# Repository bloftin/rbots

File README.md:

# rbots
RTEAM Robotics Club repository

Our club website: http://rteamrobotics.weebly.com/

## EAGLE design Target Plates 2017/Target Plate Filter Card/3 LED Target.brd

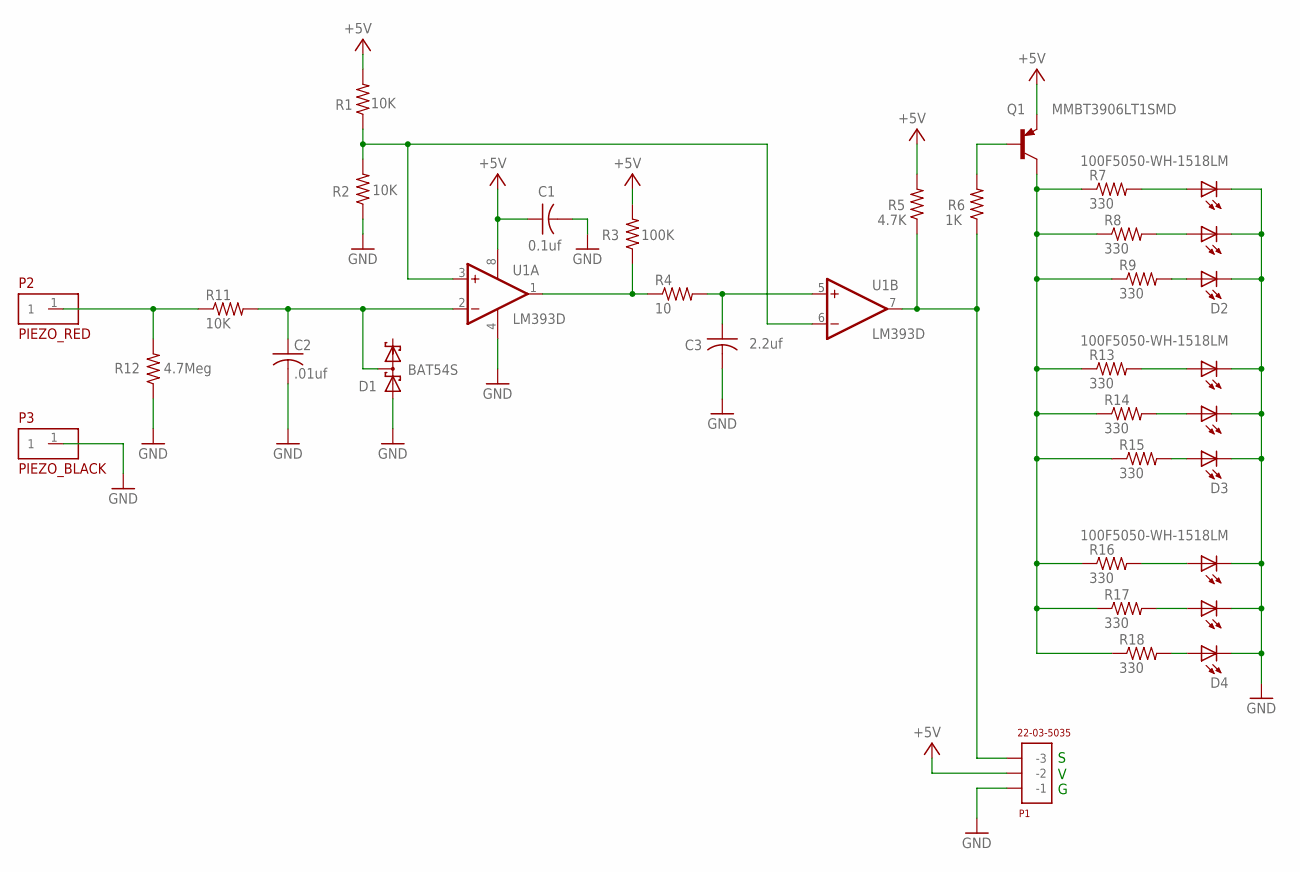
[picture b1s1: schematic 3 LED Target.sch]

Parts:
C1: 0.1uf; C0603
C2: .01uf; C0603
C3: 2.2uf; C1206
D1: BAT54S; SOT23
D2, D3, D4: 100F5050-WH-1518LM; LED5050
P1: 22-03-5035; MOLEX3_STRAIGHT
P2: PIEZO_RED; PADHOLE
P3: PIEZO_BLACK; PADHOLE
Q1: MMBT3906LT1SMD; SOT23-BEC
R1, R2, R11: 10K; R0603
R3: 100K; R0603
R4: 10; R0603
R5: 4.7K; R0603
R6: 1K; R0603
R7, R8, R9, R13, R14, R15, R16, R17, R18: 330; R0603
R12: 4.7Meg; R0603
U1: LM393D; SO08

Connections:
+5V: C1.1, P1.2 (-2), Q1.E, R1.2, R3.2, R5.2, U1.8 (V+)
GND: C1.2, C2.2, C3.2, D1.1 (A1), D2.4 (C2), D2.5 (C1), D2.6 (C), D3.4 (C2), D3.5 (C1), D3.6 (C), D4.4 (C2), D4.5 (C1), D4.6 (C), P1.1 (-1), P3.1, R2.1, R12.1, U1.4 (V-)
unnamed: P2.1, R11.1, R12.2
unnamed: C2.1, D1.3 (C1A2), R11.2, U1.2 (-IN)
unnamed: R1.1, R2.2, U1.3 (+IN), U1.6 (-IN)
unnamed: Q1.B, R6.2
unnamed: R3.1, R4.1, U1.1 (OUT)
unnamed: C3.1, R4.2, U1.5 (+IN)
unnamed: Q1.C, R7.1, R8.1, R9.1, R13.1, R14.1, R15.1, R16.1, R17.1, R18.1
unnamed: D2.1 (A), R7.2
unnamed: D2.2 (A1), R8.2
unnamed: D2.3 (A2), R9.2
unnamed: D3.1 (A), R13.2
unnamed: D3.2 (A1), R14.2
unnamed: D3.3 (A2), R15.2
unnamed: D4.1 (A), R16.2
unnamed: D4.2 (A1), R17.2
unnamed: D4.3 (A2), R18.2
unnamed: P1.3 (-3), R5.1, R6.1, U1.7 (OUT)

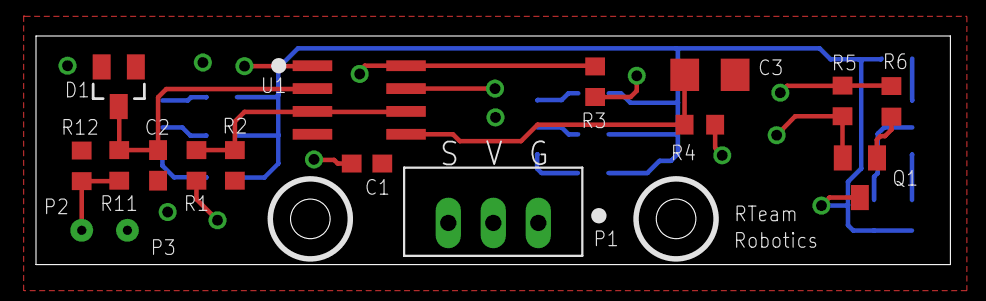
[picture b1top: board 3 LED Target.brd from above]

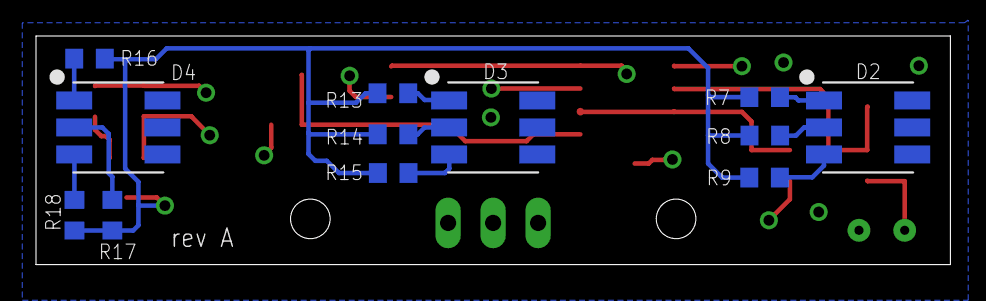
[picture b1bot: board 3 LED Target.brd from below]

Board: 4 copper layers, 50.8 x 12.7 mm, 29 parts (12 on the bottom side), 19 nets.

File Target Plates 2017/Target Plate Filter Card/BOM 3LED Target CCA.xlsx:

| Bill of Materials for 3LED Target Circuit Card Assembly
Reference Designator | Description | Manufacturer | Part Number | Distributor | Distributor Part Number | Quantity | Piece Price | Total Price
R1, R2, R11 | 10K, 0603, resistor | Vishay Dale | CRCW060310K0FKEA | Digikey | 541-10.0KHCT-ND | 3 | 0.1 | 0.30000000000000004
R3 | 100K, 0603, resistor | Vishay Dale | CRCW0603100KFKEA | Digikey | 541-100KHCT-ND | 1 | 0.1 | 0.1
R4 | 10 ohm, 0603, resistor | Vishay Dale | CRCW060310R0FKEA | Digikey | 541-10.0HCT-ND | 1 | 0.1 | 0.1
R5 | 4.7K, 0603, resistor | Vishay Dale | CRCW06034K70FKEA | Digikey | 541-4.70KHCT-ND | 1 | 0.1 | 0.1
R6 | 1K, 0603, resistor | Vishay Dale | CRCW06031K00FKEA | Digikey | 541-1.00KHCT-ND | 1 | 0.1 | 0.1
R7, R8, R9, R13, R14, R15, R16, R17, R18 | 330 ohm, 0603, resistor | Vishay Dale | CRCW0603330RFKEA | Digikey | 541-330HCT-ND | 1 | 0.1 | 0.1
R12 | 4.7 Megohm, 0603, resistor | Vishay Dale | CRCW06034M70FKEA | Digikey | 541-4.70MHCT-ND |  | 0.1 | 0.1
C1 | 0.1 uF, X7R, 0603, capacitor | Vishay Vitramon | VJ0603Y104KXXCW1BC | Digikey | 720-1379-1-ND | 1 | 0.1 | 0.1
C2 | .01 uF, X7R, 0603, capacitor | Vishay Vitramon | VJ0603Y103KXACW1BC | Digikey | 720-1531-1-ND | 1 | 0.1 | 0.1
C3 | 2.2 uF, X7R, 1206, capacitor | TDK Corp. | C3216X7R1E225K160AA | Digikey | 445-1382-1-ND | 1 | 0.24 | 0.24
D1 | Schottky dual diode, SOT23 | Vishay Semiconductor | BAT54S-E3-08 | Digikey | BAT54S-E3-08CT-ND | 1 | 0.32 | 0.32
D2, D3, D4 | Triple LED, 6000K, 15-18LM, white, (100 quantity for $7.13) | Chanzon | 100F5050-WH-1518LM | Amazon | 100F5050-WH-1518LM | 3 | 7.1300000000000002E-2 | 0.21390000000000001
Q1 | PNP transistor, SOT23 | On Semiconductor | MMBT3906LT1G | Digikey | MMBT3906LT1GOSCT-ND | 1 | 0.1 | 0.1
U1 | Dual comparator | ST Microelectronics | LM393DT | Digikey | 497-1593-1-ND | 1 | 0.39 | 0.39
P1 | 3 pin connector, keyed, 2.5 mm pitch, vertical | Molex | 22-03-5035 | Digikey | WM18887-ND | 1 | 0.5 | 0.5
 |  |  |  |  |  |  | Total | 2.8639000000000001
Misc other parts not on Circuit card assembly
 | Description | Manufacturer | Part Number | Distributor | Distributor Part Number | Quantity | Piece Price
 | Piezo Buzzer, 24mm, plastic housing, wire leads | CUI Inc. | CEP-1110 | Digikey | 102-1144-ND | 1 | 1.78
 | Latex Tubing, #804, 3/8in OD, 1/4in ID, 1/16in wall thickness, black, 1 ft long | Kent Elastomer | #804, 1 foot | Amazon | Serach: latex tubing (#804) 1 FT BLACK | 1 | 3.99
 | Black velcro, 7 in x 0.4 in |  |  |  |  | 1
 | 2mm bolts |  |  | McMaster-Carr |  | 4
 | 2mm nuts |  |  | McMaster-Carr |  | 6

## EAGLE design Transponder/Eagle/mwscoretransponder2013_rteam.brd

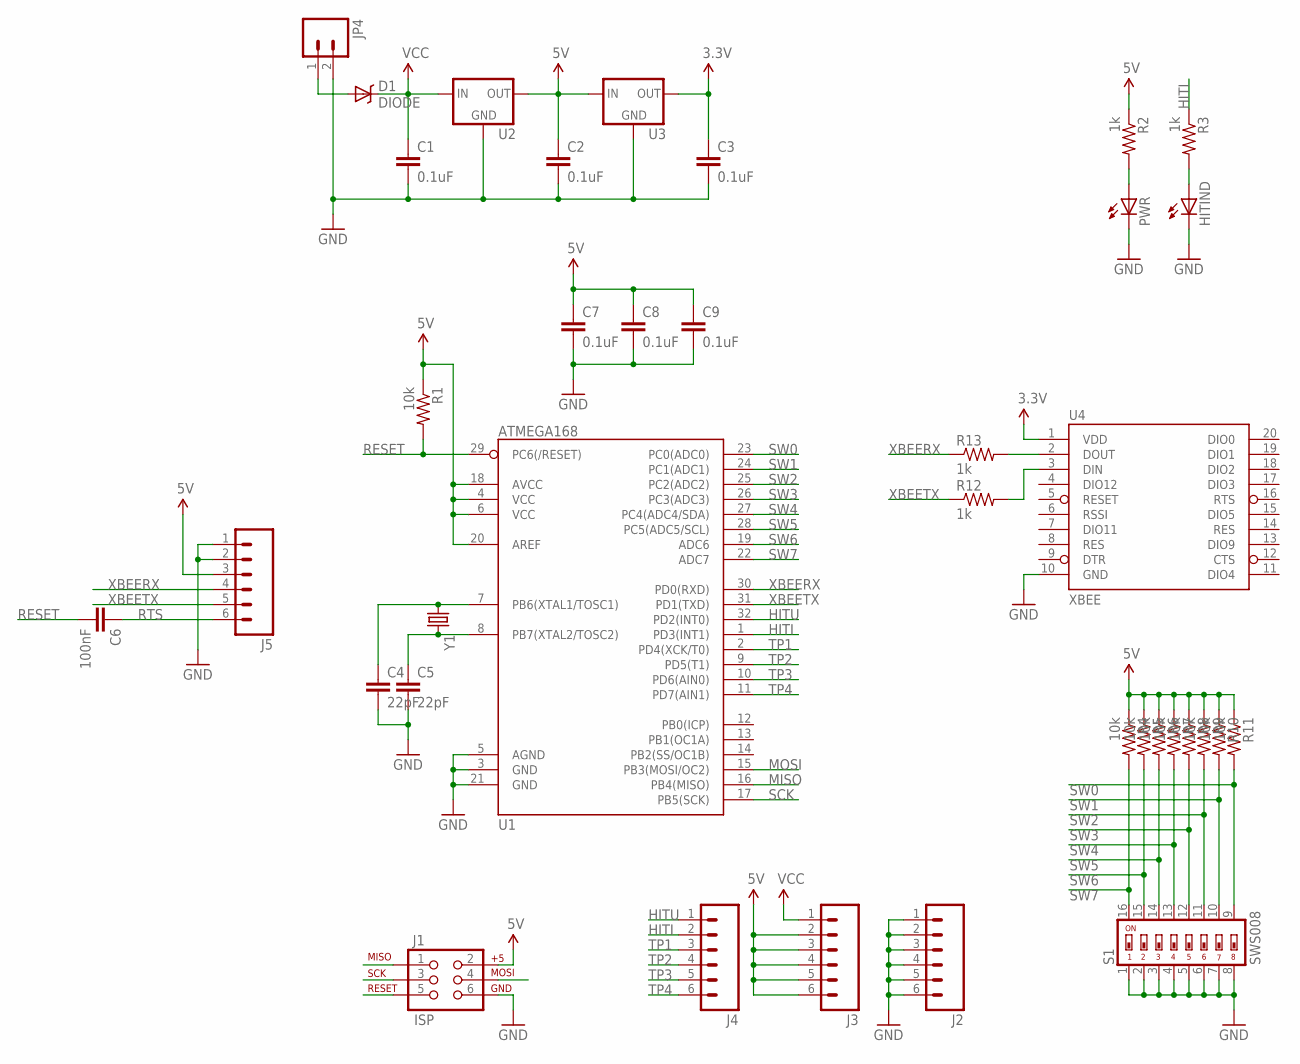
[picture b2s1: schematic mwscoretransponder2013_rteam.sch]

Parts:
C1, C2, C3, C7, C8, C9: 0.1uF; 0603-CAP
C4, C5: 22pF; 0603-CAP
C6: 100nF; 0603-CAP
D1: DIODE; SMA-DIODE
HITIND: LED0603; LED-0603
J1: ISP; 2X3
J2, J3, J4, J5: M06SIP; 1X06
JP4: M023.5MM_LOCK; SCREWTERMINAL-3.5MM-2_LOCK
PWR: LED0603; LED-0603
R1, R4, R5, R6, R7, R8, R9, R10, R11: 10k; 0603-RES
R2, R3, R12, R13: 1k; 0603-RES
S1: SWS008; SMS-008
U1: ATMEGA168; TQFP32-08
U2, U3: V_REG_MIC2920; SOT223
U4: XBEE; XBEE-SMD
Y1: CRYSTAL5X3; CRYSTAL-SMD-5X3

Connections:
3.3V: C3.1, U3.3 (OUT), U4.1 (VDD)
5V: C2.1, C7.1, C8.1, C9.1, J1.2, J3.2, J3.3, J3.4, J3.5, J3.6, J5.3, R1.1, R2.1, R4.1, R5.1, R6.1, R7.1, R8.1, R9.1, R10.1, R11.1, U1.4 (VCC), U1.6 (VCC), U1.18 (AVCC), U1.20 (AREF), U2.3 (OUT), U3.1 (IN)
GND: C1.2, C2.2, C3.2, C4.2, C5.2, C7.2, C8.2, C9.2, HITIND.C, J1.6, J2.1, J2.2, J2.3, J2.4, J2.5, J2.6, J5.1, J5.2, JP4.2, PWR.C, S1.1, S1.2, S1.3, S1.4, S1.5, S1.6, S1.7, S1.8, U1.3 (GND), U1.5 (AGND), U1.21 (GND), U2.2 (GND), U3.2 (GND), U4.10 (GND)
HITI: J4.2, R3.1, U1.1 (PD3(INT1))
HITU: J4.1, U1.32 (PD2(INT0))
MISO: J1.1, U1.16 (PB4(MISO))
MOSI: J1.4, U1.15 (PB3(MOSI/OC2))
unnamed: PWR.A, R2.2
unnamed: HITIND.A, R3.2
unnamed: C4.1, U1.7 (PB6(XTAL1/TOSC1)), Y1.1
unnamed: D1.A, JP4.1
unnamed: C5.1, U1.8 (PB7(XTAL2/TOSC2)), Y1.3 (2)
unnamed: R13.2, U4.2 (DOUT)
unnamed: R12.2, U4.3 (DIN)
RESET: C6.2, J1.5, R1.2, U1.29 (PC6(/RESET))
RTS: C6.1, J5.6
SCK: J1.3, U1.17 (PB5(SCK))
SW0: R11.2, S1.9, U1.23 (PC0(ADC0))
SW1: R10.2, S1.10, U1.24 (PC1(ADC1))
SW2: R9.2, S1.11, U1.25 (PC2(ADC2))
SW3: R8.2, S1.12, U1.26 (PC3(ADC3))
SW4: R7.2, S1.13, U1.27 (PC4(ADC4/SDA))
SW5: R6.2, S1.14, U1.28 (PC5(ADC5/SCL))
SW6: R5.2, S1.15, U1.19 (ADC6)
SW7: R4.2, S1.16, U1.22 (ADC7)
TP1: J4.3, U1.2 (PD4(XCK/T0))
TP2: J4.4, U1.9 (PD5(T1))
TP3: J4.5, U1.10 (PD6(AIN0))
TP4: J4.6, U1.11 (PD7(AIN1))
VCC: C1.1, D1.C, J3.1, U2.1 (IN)
XBEERX: J5.4, R13.1, U1.30 (PD0(RXD))
XBEETX: J5.5, R12.1, U1.31 (PD1(TXD))

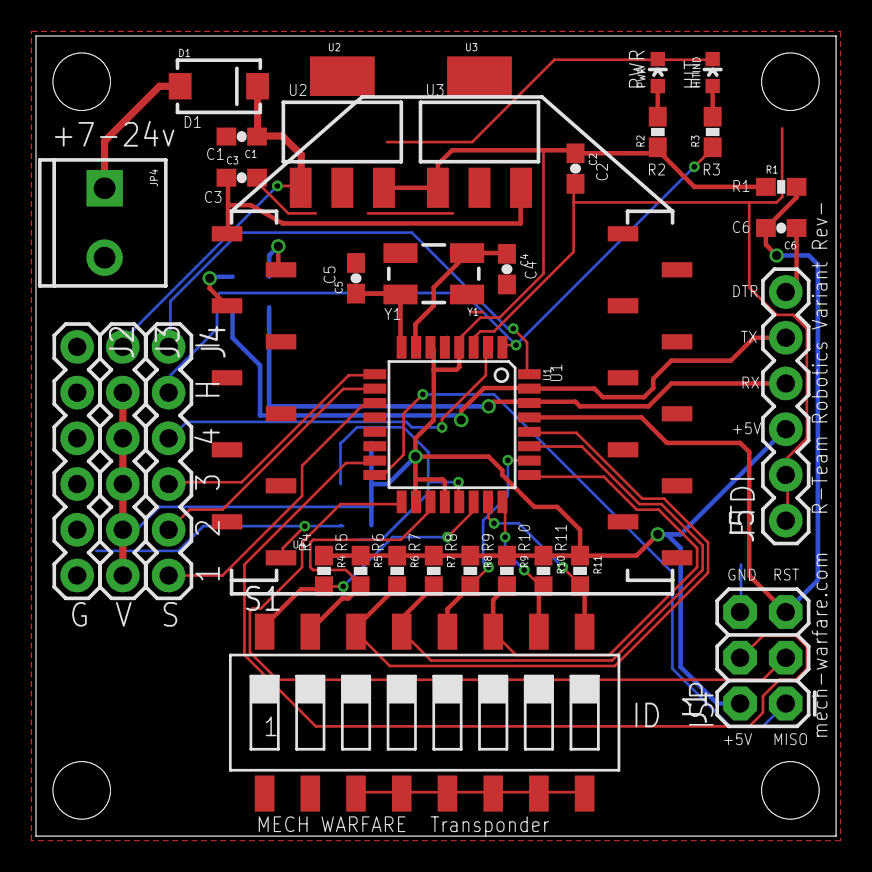
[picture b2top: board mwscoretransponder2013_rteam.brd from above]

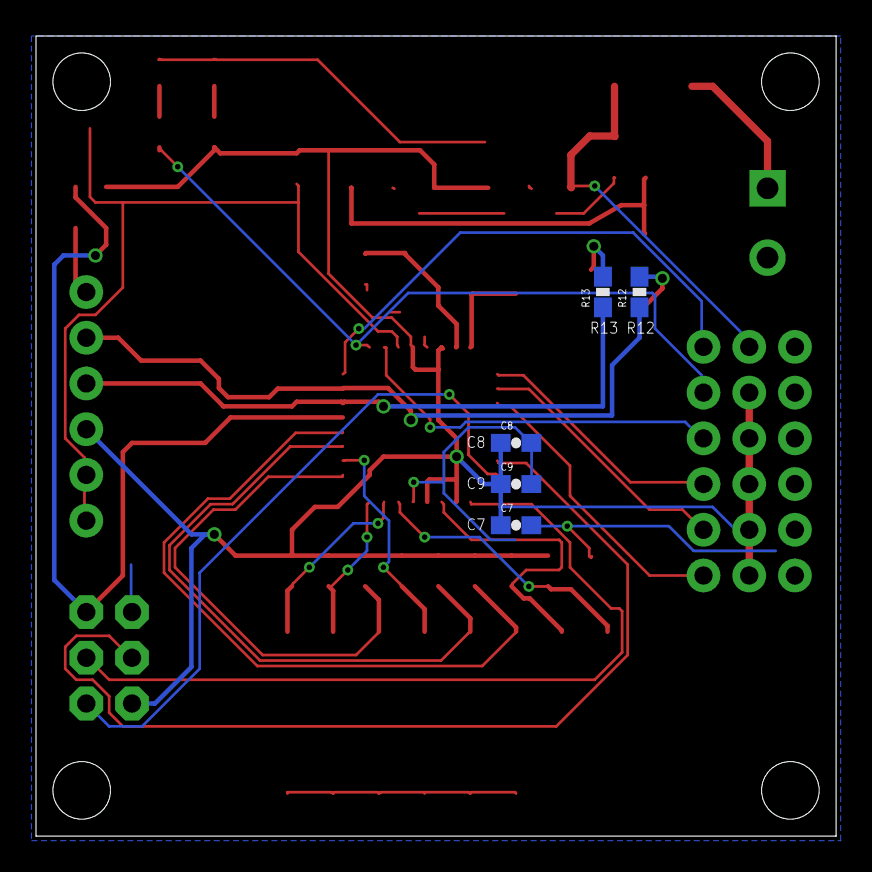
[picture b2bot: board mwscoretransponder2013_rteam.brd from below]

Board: 2 copper layers, 44.5 x 44.5 mm, 37 parts (5 on the bottom side), 32 nets.

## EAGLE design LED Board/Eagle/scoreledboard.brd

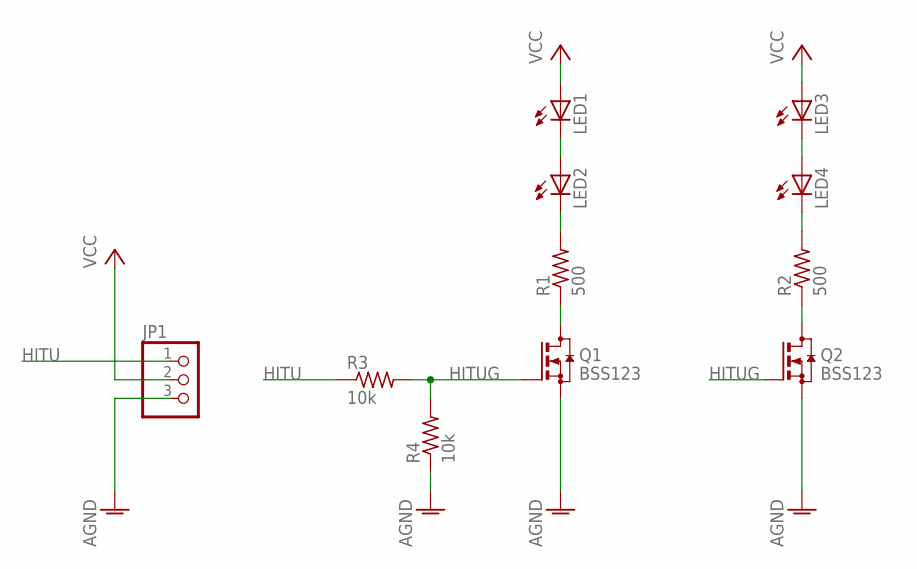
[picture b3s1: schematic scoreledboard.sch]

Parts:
JP1: PINHD-1X3; 1X03
LED1, LED2, LED3, LED4: LEDCHIPLED_1206; CHIPLED_1206
Q1, Q2: BSS123; SOT23
R1, R2: 500; R1206
R3, R4: 10k; R1206

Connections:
AGND: JP1.3, Q1.2 (S), Q2.2 (S), R4.1
HITU: JP1.1, R3.1
HITUG: Q1.1 (G), Q2.1 (G), R3.2, R4.2
unnamed: LED1.C, LED2.A
unnamed: LED2.C, R1.2
unnamed: Q1.3 (D), R1.1
unnamed: LED3.C, LED4.A
unnamed: LED4.C, R2.2
unnamed: Q2.3 (D), R2.1
VCC: JP1.2, LED1.A, LED3.A

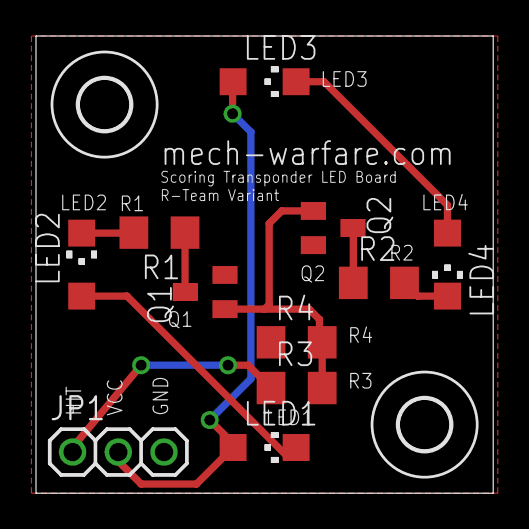
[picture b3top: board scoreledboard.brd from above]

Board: 2 copper layers, 25.4 x 25.4 mm, 13 parts (0 on the bottom side), 10 nets.

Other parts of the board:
U$1, U$2: 2,8

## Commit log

2015-04-29 Initial LED and transponder design
    Initial LED and transponder design for Mech Warfare target plates
2015-04-29 Archive test
    Archive test
2015-04-29 archive
    archive
2015-04-30 initial target plate design
    initial target plate design
2015-04-30 Archive lego mindstorms
    Archive lego mindstorms
2015-04-30 Archive Arduino
    Archive Arduino
2015-04-30 Archive Arduino 2
    Archive Arduino 2
2015-04-30 Archive Droid
    Archive Droid
2015-04-30 Archive Droid 2
    Archive Droid 2
2015-04-30 Archive Droid 3
    Archive Droid 3
2015-04-30 Archive Droid 4
    Archive Droid 4
2015-04-30 Archive Droid 5
    Archive Droid 5
2015-04-30 Archive Droid 6
    Archive Droid 6
2015-04-30 Archive Droid 7
    Archive Droid 7
2015-04-30 Archive Droid 8
    Archive Droid 8
2015-04-30 Archive cores
    Archive cores
2015-04-30 archive Bioloid
    archive Bioloid
2015-04-30 archive blink 2
    archive blink 2
2015-04-30 archive blink 3
    archive blink 3
2015-04-30 archive Dynamixel
    archive Dynamixel
2015-10-03 Version 1 of the Club Mech Warrior Design
    First snapshot of all the Club Mech parts, note this is the latest
    design from Joey who did some updates after receiving it from Jeff.
2015-10-03 Mech Version 1 initial snapshot
    Mech Version 1 initial snapshot
2015-10-03 Initial Mech Parts version 1 for loader
    Initial Mech Parts version 1 for loader
2015-10-03 Initial Mech Parts Version 1
    Initial Mech Parts Version 1
2016-03-16 added Don's guide to target plate assembly
    added Don's guide to target plate assembly
2016-05-12 Add MechLocalization
2016-05-12 moved localization files
2016-09-04 Update motor.h
    Fixed error
2016-12-29 Init commit. This code is what ran on Thorn up till 12/28/2016. Code loaded when Mike Mazzucco received bot.
2017-02-01 2017 Target Plate Updates
2017-02-03 Mech99
2017-02-03 AEG Gearbox
2017-02-04 Mech99 Gun igs files
2019-08-22 added a link to our website

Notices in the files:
parts and their libraries:
SparkFun: Licensing: CC v3.0 Share-Alike You are welcome to use this library for commercial purposes.
